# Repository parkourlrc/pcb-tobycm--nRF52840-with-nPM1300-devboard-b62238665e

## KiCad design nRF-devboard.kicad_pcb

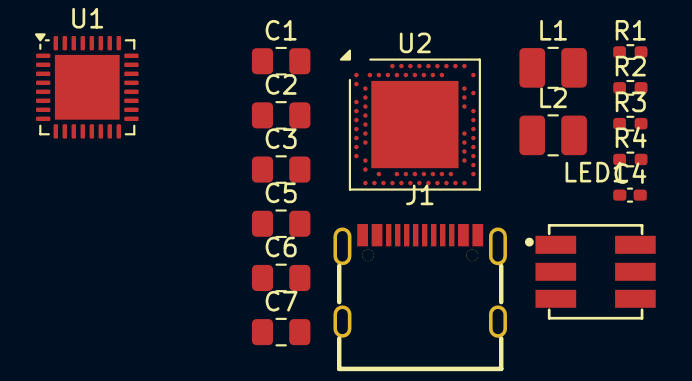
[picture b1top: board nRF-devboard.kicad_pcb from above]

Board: 2 copper layers, 17 parts (0 on the bottom side), 19 nets, no tracks yet.

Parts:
C1, C2, C3, C5, C6: 10uF; C_0805_2012Metric_Pad1.18x1.45mm_HandSolder
C4: 1uF; C_0402_1005Metric_Pad0.74x0.62mm_HandSolder
C7: 2.2uF; C_0805_2012Metric_Pad1.18x1.45mm_HandSolder
J1: GT-USB-7010ASV; USB-C-SMD_G-SWITCH_GT-USB-7010ASV
L1, L2: 2.2uH; L_1008_2520Metric_Pad1.43x2.20mm_HandSolder
LED1: TC5050RGBF08-3CJH-AF53A; LED-SMD_6P-L5.0-W5.0-TL_TC5050RGBF08
R1, R2: 390k; R_0402_1005Metric_Pad0.72x0.64mm_HandSolder
R3, R4: 10k; R_0402_1005Metric_Pad0.72x0.64mm_HandSolder
U1: nPM1300; QFN-32-1EP_5x5mm_P0.5mm_EP3.6x3.6mm
U2: nRF52840; Nordic_AQFN-73-1EP_7x7mm_P0.5mm

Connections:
+2.7V: C5.1, L1.1, U1.1 (VOUT1), U2.A22 (VDD), U2.AD14 (VDD), U2.AD23 (VDD), U2.B1 (VDD), U2.W1 (VDD), U2.Y2 (VDDH)
+3.3V: C6.1, L2.1, U1.32 (VOUT2)
/CC1: J1.A5 (CC1), U1.23 (CC1)
/CC2: J1.B5 (CC2), U1.24 (CC2)
GND: C1.2, C2.2, C3.2, C4.2, C5.2, C6.2, C7.2, J1.1 (SHELL), J1.2 (SHELL), J1.3 (SHELL), J1.4 (SHELL), J1.A1B12 (GND), J1.B1A12 (GND), R1.1, R2.1, U1.2 (PVSS1), U1.6 (PVSS2), U1.33 (AVSS), U2.B7 (VSS), U2.EP (VSS), U2.F23 (VSS_PA)
unnamed: J1.A7 (DN1), J1.B7 (DN2), U2.AD4 (D-)
unnamed: J1.A6 (DP1), J1.B6 (DP2), U2.AD6 (D+)
unnamed: LED1.6 (-), U1.25 (LED0)
unnamed: LED1.5 (-), U1.26 (LED1)
unnamed: LED1.4 (-), U1.27 (LED2)
unnamed: L1.2, U1.3 (SW1)
unnamed: L2.2, U1.5 (SW2)
unnamed: R2.2, U1.17 (VSET1)
unnamed: R1.2, U1.16 (VSET2)
SCL: R3.1, U1.14 (SCL)
SDA: R4.1, U1.13 (SDA)
VBAT: C7.1, U1.19 (VBAT)
VBUS: J1.A4B9 (VBUS), J1.B4A9 (VBUS), U1.21 (VBUS)
VSYS: C1.1, C2.1, C3.1, C4.1, LED1.1 (+), LED1.2 (+), LED1.3 (+), R3.2, R4.2, U1.4 (PVDD), U1.20 (VSYS), U1.22 (VBUSOUT)
